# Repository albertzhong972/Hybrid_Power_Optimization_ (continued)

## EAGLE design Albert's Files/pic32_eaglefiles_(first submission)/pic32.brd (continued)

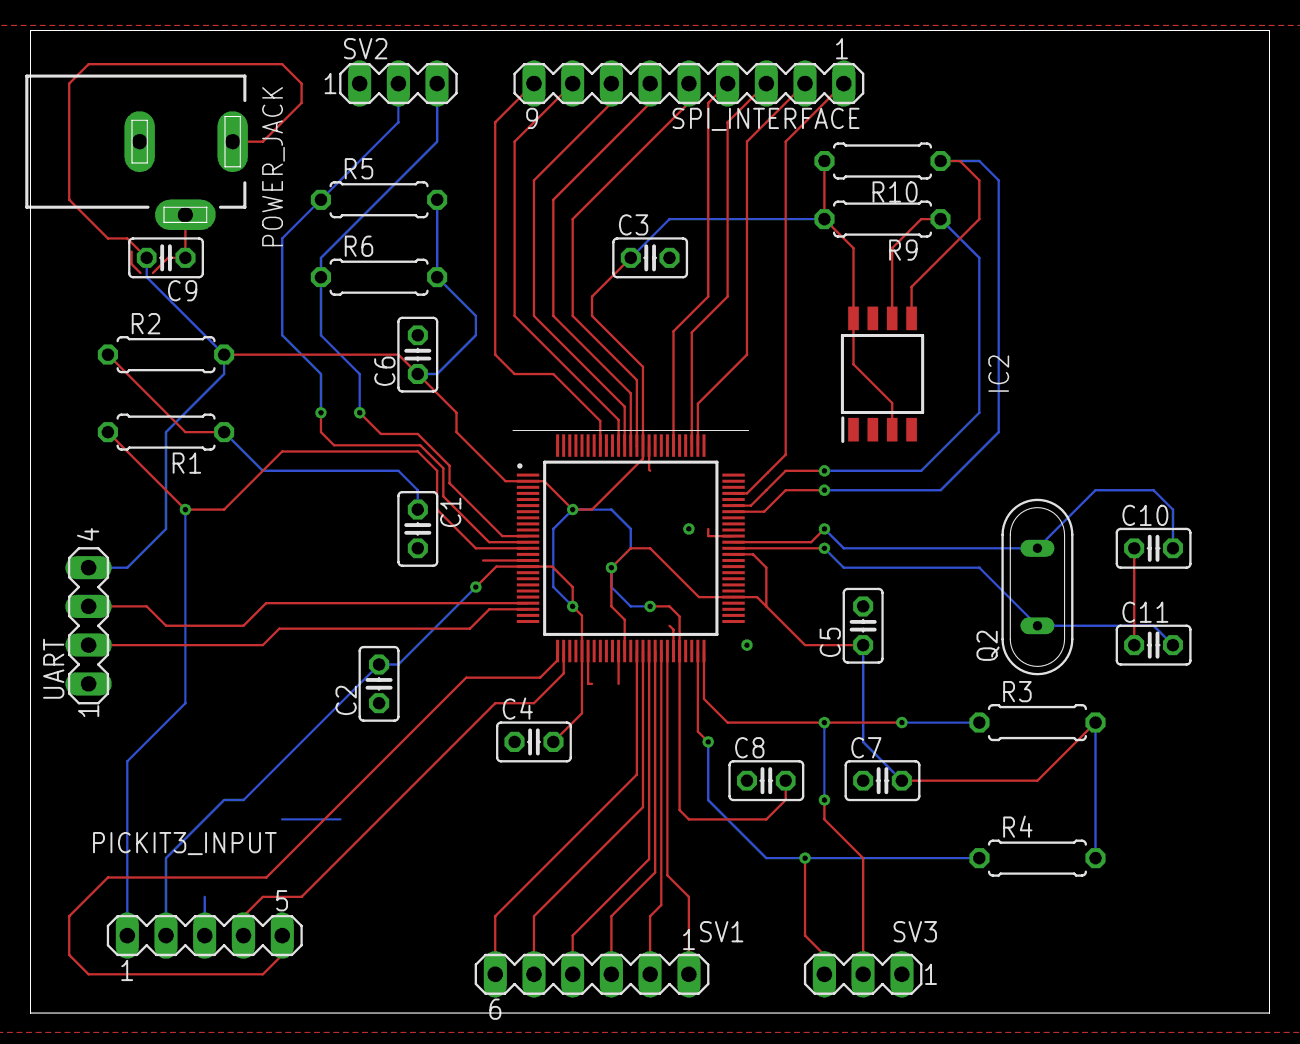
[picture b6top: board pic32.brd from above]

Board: 2 copper layers, 81.3 x 64.4 mm, 29 parts (0 on the bottom side), 31 nets.
